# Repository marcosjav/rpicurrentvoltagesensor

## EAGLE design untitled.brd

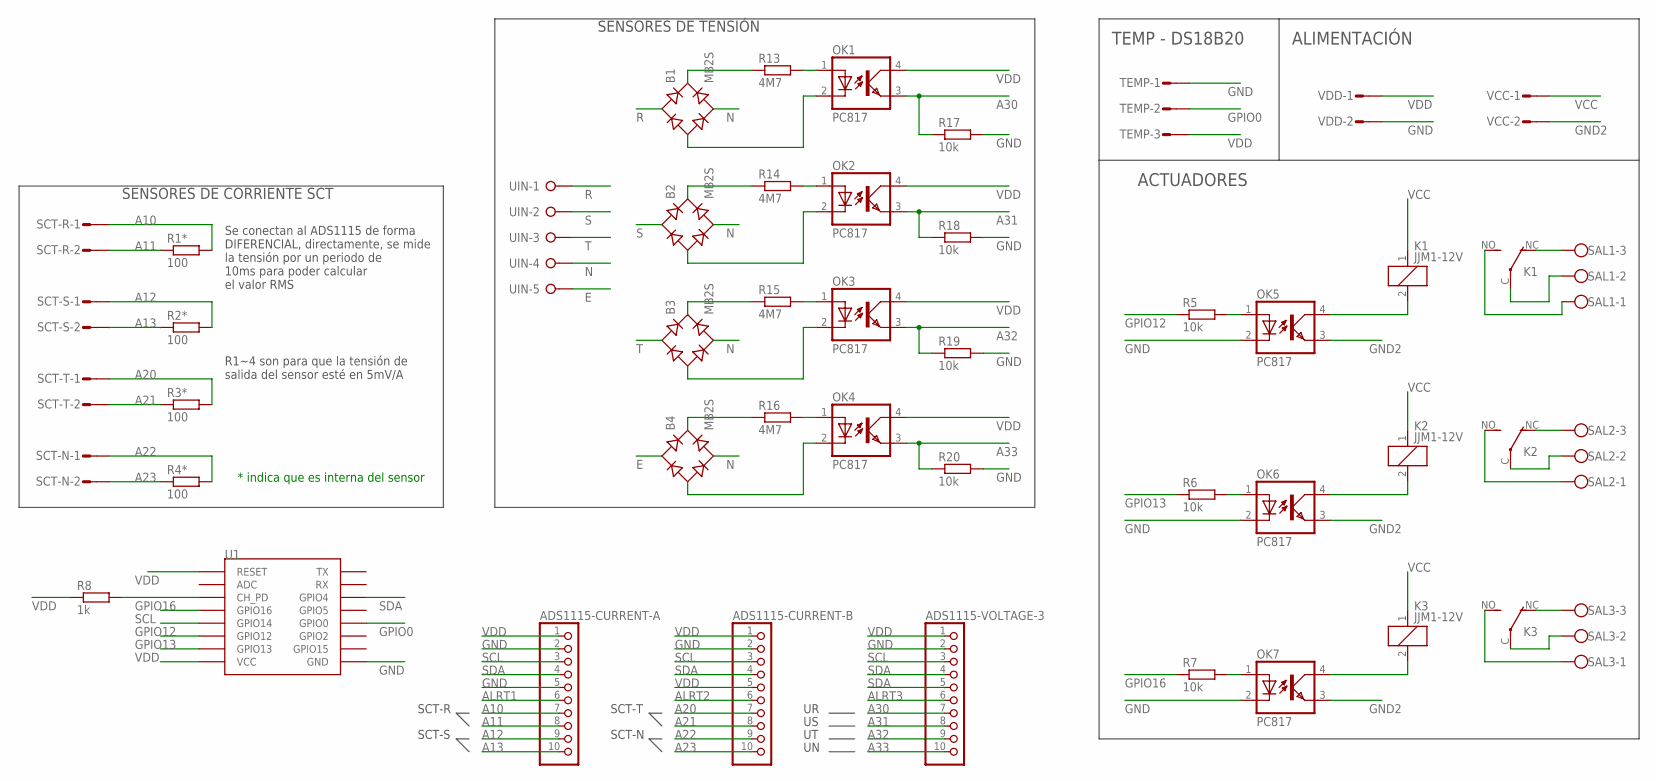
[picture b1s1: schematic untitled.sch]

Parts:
ADS1115-CURRENT-A, ADS1115-CURRENT-B, ADS1115-VOLTAGE-3: PINHD-1X10; 1X10
B1, B2, B3, B4: MB2S; SOIC-4
K1, K2, K3: JJM1-12V; JJM1C
OK1, OK2, OK3, OK4, OK5, OK6, OK7: PC817; DIL04
R1*, R2*, R3*, R4*: 100; M0805
R5, R6, R7, R17, R18, R19, R20: 10k; M0805
R8: 1k; M0805
R13, R14, R15, R16: 4M7; M0805
SAL1, SAL2, SAL3: W237-103
SCT-N: S02P
SCT-R: S02P
SCT-S: S02P
SCT-T: S02P
TEMP: S03P
U1: ESP12SMD; ESP12-SMD
UIN: W237-05P; W237-5P
VCC: S02P
VDD: S02P

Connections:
A10: ADS1115-CURRENT-A.7, R1*.2, SCT-R.1; also elsewhere on the board
A11: ADS1115-CURRENT-A.8, R1*.1, SCT-R.2; also elsewhere on the board
A12: ADS1115-CURRENT-A.9, R2*.2, SCT-S.1; also elsewhere on the board
A13: ADS1115-CURRENT-A.10, R2*.1, SCT-S.2; also elsewhere on the board
A20: ADS1115-CURRENT-B.7, R3*.2, SCT-T.1; also elsewhere on the board
A21: ADS1115-CURRENT-B.8, R3*.1, SCT-T.2; also elsewhere on the board
A22: ADS1115-CURRENT-B.9, R4*.2, SCT-N.1; also elsewhere on the board
A23: ADS1115-CURRENT-B.10, R4*.1, SCT-N.2; also elsewhere on the board
A30: ADS1115-VOLTAGE-3.7, OK1.3 (EMIT), R17.1
A31: ADS1115-VOLTAGE-3.8, OK2.3 (EMIT), R18.1
A32: ADS1115-VOLTAGE-3.9, OK3.3 (EMIT), R19.1
A33: ADS1115-VOLTAGE-3.10, OK4.3 (EMIT), R20.1
ALRT1: ADS1115-CURRENT-A.6
ALRT2: ADS1115-CURRENT-B.6
ALRT3: ADS1115-VOLTAGE-3.6
E: B4.~1 (AC1), UIN.5
GND: ADS1115-CURRENT-A.2, ADS1115-CURRENT-A.5, ADS1115-CURRENT-B.2, ADS1115-VOLTAGE-3.2, OK5.2 (C), OK6.2 (C), OK7.2 (C), R17.2, R18.2, R19.2, R20.2, TEMP.1, U1.GND, VDD.2
GND2: OK5.3 (EMIT), OK6.3 (EMIT), OK7.3 (EMIT), VCC.2
GPIO0: TEMP.2, U1.GPIO0
GPIO12: R5.1, U1.GPIO12
GPIO13: R6.1, U1.GPIO13
GPIO16: R7.1, U1.GPIO16
N: B1.~2 (AC2), B2.~2 (AC2), B3.~2 (AC2), B4.~2 (AC2), UIN.4
unnamed: K1.C, SAL1.2
unnamed: K1.NO (S), SAL1.1
unnamed: K1.NC (O), SAL1.3
unnamed: K1.2, OK5.4 (COL)
unnamed: K2.2, OK6.4 (COL)
unnamed: K3.2, OK7.4 (COL)
unnamed: OK5.1 (A), R5.2
unnamed: OK2.1 (A), R14.2
unnamed: OK1.1 (A), R13.2
unnamed: B2.+, R14.1
unnamed: B1.+, R13.1
unnamed: B1.-, OK1.2 (C)
unnamed: B2.-, OK2.2 (C)
unnamed: OK3.1 (A), R15.2
unnamed: B3.+, R15.1
unnamed: B3.-, OK3.2 (C)
unnamed: OK4.1 (A), R16.2
unnamed: B4.+, R16.1
unnamed: B4.-, OK4.2 (C)
unnamed: R8.2, U1.CH_PD
unnamed: K2.NC (O), SAL2.3
unnamed: K2.C, SAL2.2
unnamed: K2.NO (S), SAL2.1
unnamed: K3.C, SAL3.2
unnamed: K3.NC (O), SAL3.3
unnamed: K3.NO (S), SAL3.1
unnamed: OK6.1 (A), R6.2
unnamed: OK7.1 (A), R7.2
R: B1.~1 (AC1), UIN.1
S: B2.~1 (AC1), UIN.2
SCL: ADS1115-CURRENT-A.3, ADS1115-CURRENT-B.3, ADS1115-VOLTAGE-3.3, U1.GPIO14
SDA: ADS1115-CURRENT-A.4, ADS1115-CURRENT-B.4, ADS1115-VOLTAGE-3.4, ADS1115-VOLTAGE-3.5, U1.GPIO4
T: B3.~1 (AC1), UIN.3
VCC: K1.1, K2.1, K3.1, VCC.1
VDD: ADS1115-CURRENT-A.1, ADS1115-CURRENT-B.1, ADS1115-CURRENT-B.5, ADS1115-VOLTAGE-3.1, OK1.4 (COL), OK2.4 (COL), OK3.4 (COL), OK4.4 (COL), R8.1, TEMP.3, U1.RESET, U1.VCC, VDD.1

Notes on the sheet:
SCT-R
SCT-S
SCT-T
SCT-N
SENSORES DE CORRIENTE SCT
Se conectan al ADS1115 de forma DIFERENCIAL, directamente, se mide la tensión por un periodo de 10ms para poder calcular el valor RMS
R1~4 son para que la tensión de salida del sensor esté en 5mV/A
SENSORES DE TENSIÓN
ACTUADORES
TEMP - DS18B20
ALIMENTACIÓN
* indica que es interna del sensor

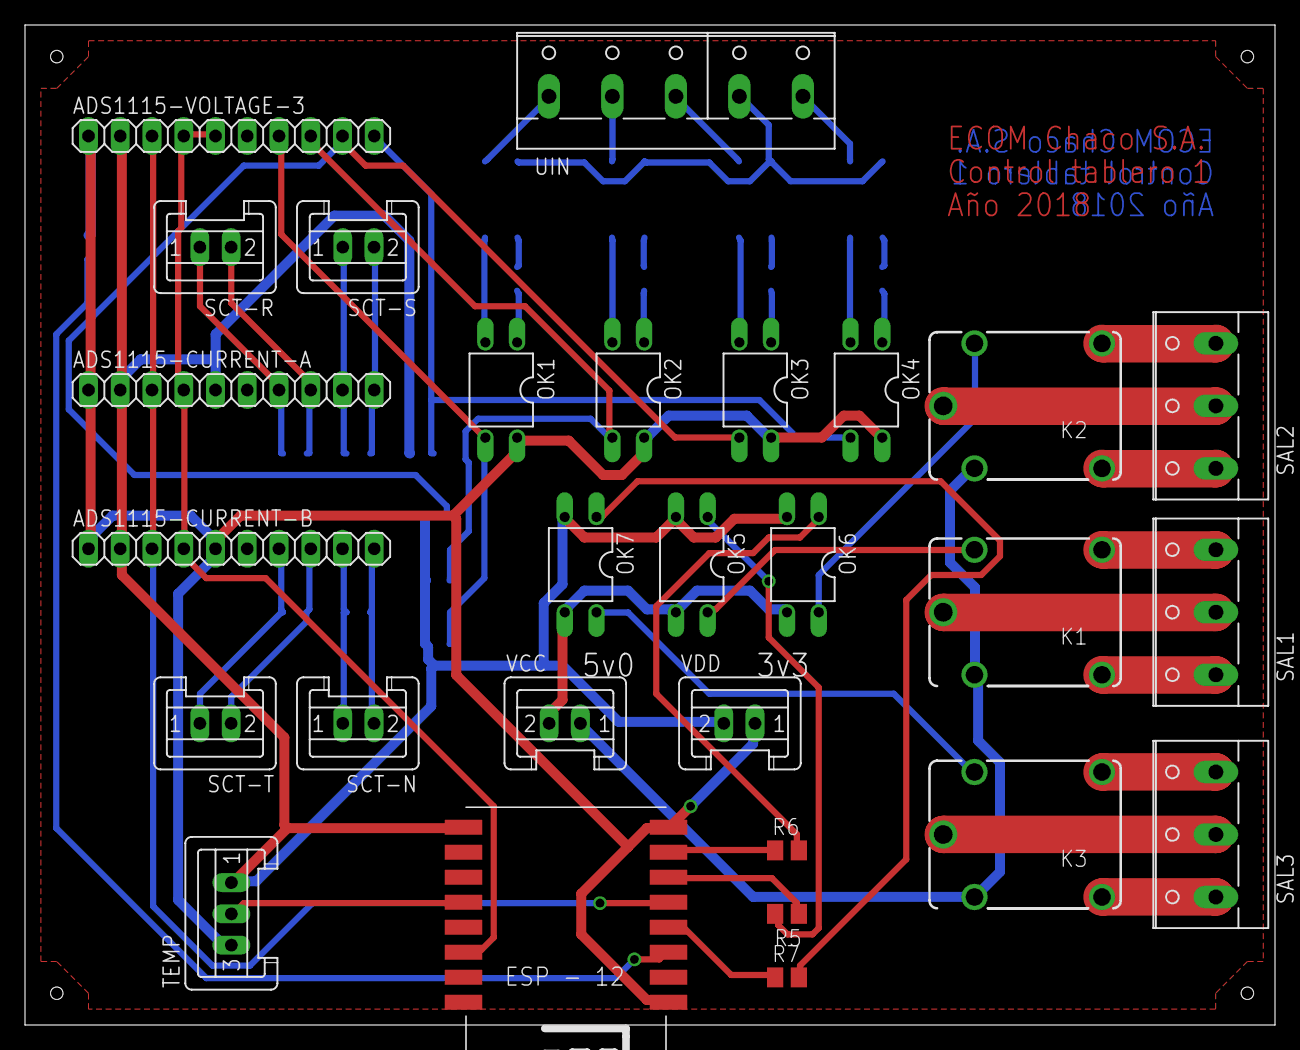
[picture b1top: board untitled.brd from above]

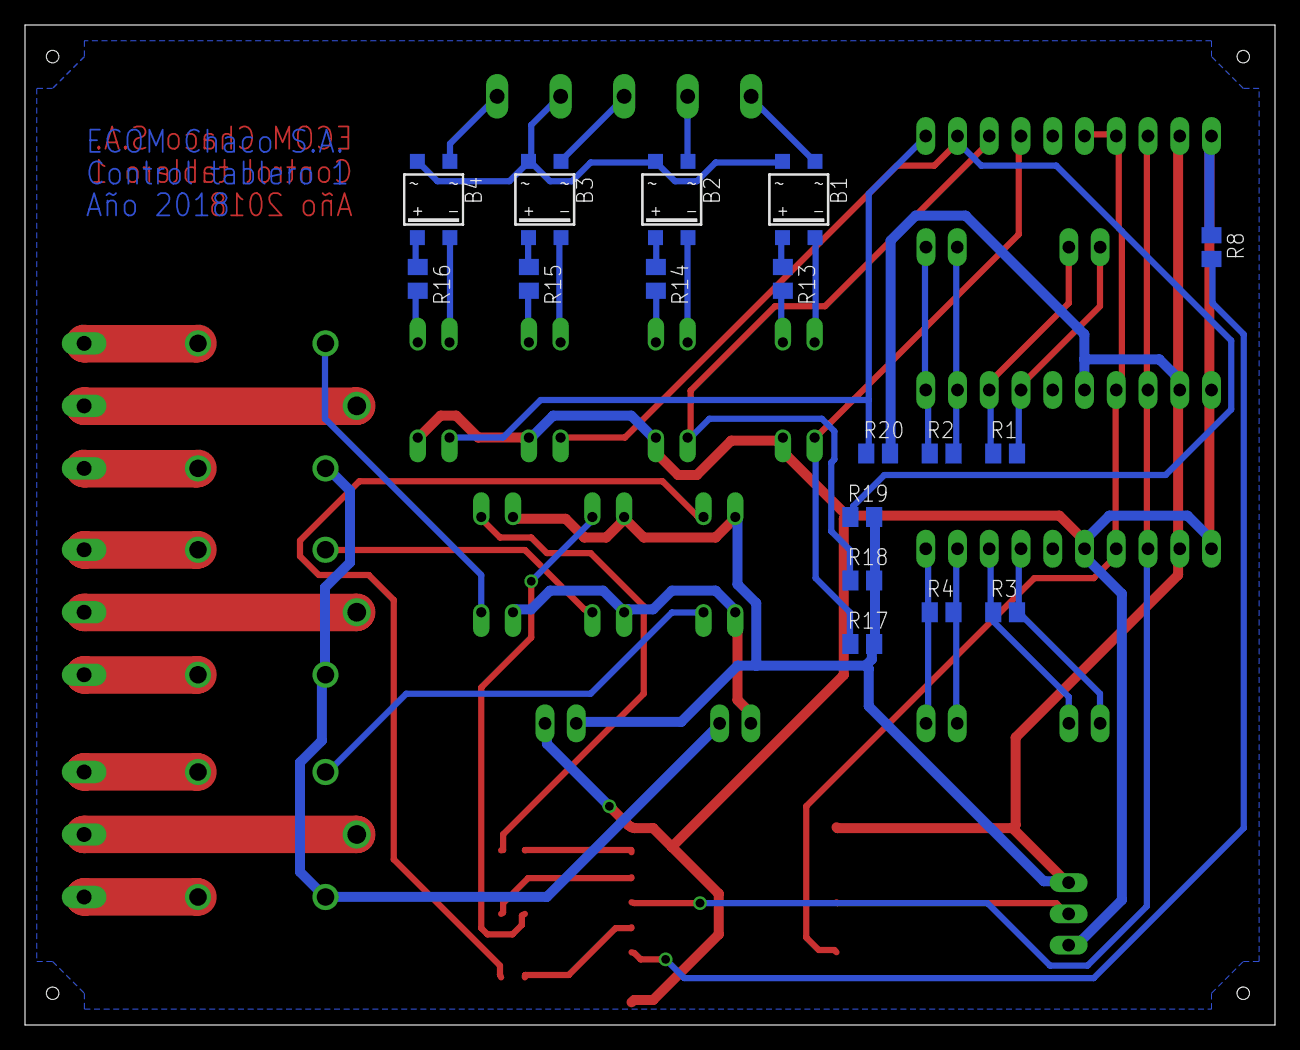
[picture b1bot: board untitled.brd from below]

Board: 2 copper layers, 100.0 x 80.0 mm, 45 parts (17 on the bottom side), 55 nets.

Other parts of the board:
R1, R2, R3, R4: 100; M0805

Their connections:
A10: R1.2; also elsewhere on the board
A11: R1.1; also elsewhere on the board
A12: R2.2; also elsewhere on the board
A13: R2.1; also elsewhere on the board
A20: R3.2; also elsewhere on the board
A21: R3.1; also elsewhere on the board
A22: R4.2; also elsewhere on the board
A23: R4.1; also elsewhere on the board

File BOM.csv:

Part;Value;Device;Package;Description
ADS1115-CURRENT-A;;PINHD-1X10;1X10;PIN HEADER
ADS1115-CURRENT-B;;PINHD-1X10;1X10;PIN HEADER
ADS1115-VOLTAGE-3;;PINHD-1X10;1X10;PIN HEADER
B1;MB2S;MB2S;SOIC-4;Bridge Rectifier
B2;MB2S;MB2S;SOIC-4;Bridge Rectifier
B3;MB2S;MB2S;SOIC-4;Bridge Rectifier
B4;MB2S;MB2S;SOIC-4;Bridge Rectifier
K1;JJM1-12V;JJM1-12V;JJM1C;HALF-SIZE AUTOMOTIVE RELAY NAiS
K2;JJM1-12V;JJM1-12V;JJM1C;HALF-SIZE AUTOMOTIVE RELAY NAiS
K3;JJM1-12V;JJM1-12V;JJM1C;HALF-SIZE AUTOMOTIVE RELAY NAiS
OK1;PC817;PC817;DIL04;SHARP OPTO COUPLER
OK2;PC817;PC817;DIL04;SHARP OPTO COUPLER
OK3;PC817;PC817;DIL04;SHARP OPTO COUPLER
OK4;PC817;PC817;DIL04;SHARP OPTO COUPLER
OK5;PC817;PC817;DIL04;SHARP OPTO COUPLER
OK6;PC817;PC817;DIL04;SHARP OPTO COUPLER
OK7;PC817;PC817;DIL04;SHARP OPTO COUPLER
R1*;100;R-EU_M0805;M0805;RESISTOR, European symbol
R2*;100;R-EU_M0805;M0805;RESISTOR, European symbol
R3*;100;R-EU_M0805;M0805;RESISTOR, European symbol
R4*;100;R-EU_M0805;M0805;RESISTOR, European symbol
R5;10k;R-EU_M0805;M0805;RESISTOR, European symbol
R6;10k;R-EU_M0805;M0805;RESISTOR, European symbol
R7;10k;R-EU_M0805;M0805;RESISTOR, European symbol
R8;1k;R-EU_M0805;M0805;RESISTOR, European symbol
R13;4M7;R-EU_M0805;M0805;RESISTOR, European symbol
R14;4M7;R-EU_M0805;M0805;RESISTOR, European symbol
R15;4M7;R-EU_M0805;M0805;RESISTOR, European symbol
R16;4M7;R-EU_M0805;M0805;RESISTOR, European symbol
R17;10k;R-EU_M0805;M0805;RESISTOR, European symbol
R18;10k;R-EU_M0805;M0805;RESISTOR, European symbol
R19;10k;R-EU_M0805;M0805;RESISTOR, European symbol
R20;10k;R-EU_M0805;M0805;RESISTOR, European symbol
SAL1;;W237-103;W237-103;WAGO SCREW CLAMP
SAL2;;W237-103;W237-103;WAGO SCREW CLAMP
SAL3;;W237-103;W237-103;WAGO SCREW CLAMP
SCT-N;;S02P;S02P;AMP MT CONNECTOR
SCT-R;;S02P;S02P;AMP MT CONNECTOR
SCT-S;;S02P;S02P;AMP MT CONNECTOR
SCT-T;;S02P;S02P;AMP MT CONNECTOR
TEMP;;S03P;S03P;AMP MT CONNECTOR
U1;;ESP12SMD;ESP12-SMD;ESP8266 Wifi module 12
UIN;;W237-05P;W237-5P;WAGO SREW CLAMP
VCC;;S02P;S02P;AMP MT CONNECTOR
VDD;;S02P;S02P;AMP MT CONNECTOR

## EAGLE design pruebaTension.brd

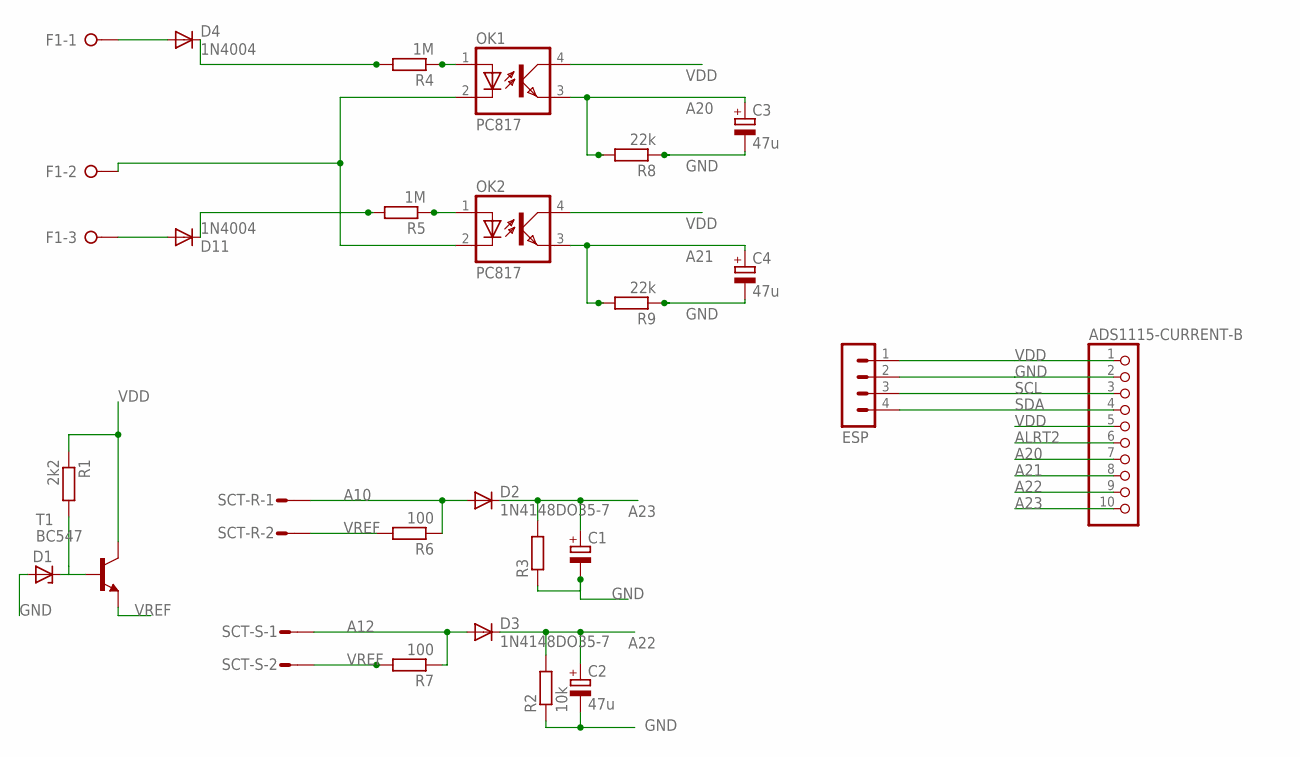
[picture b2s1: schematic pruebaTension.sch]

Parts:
ADS1115-CURRENT-B: PINHD-1X10; 1X10
C1: CPOL-EUE2.5-7; E2,5-7
C2, C3, C4: 47u; E2,5-7
D1: ZENER-DIODEZD-2.5; ZDIO-2.5
D2, D3: 1N4148DO35-7; DO35-7
D4, D11: 1N4004; DO41-10
ESP: MA04-1
F1: W237-3E
OK1, OK2: PC817; DIL04
R1: 2k2; 0204V
R2: 10k; 0204V
R3: R-EU_0204/2V; 0204V
R4, R5: 1M; 0204V
R6, R7: 100; 0204V
R8, R9: 22k; 0204V
SCT-R: S02P
SCT-S: S02P
T1: BC547; TO92

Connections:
A10: D2.A, R6.1, SCT-R.1
A12: D3.A, R7.1, SCT-S.1
A20: ADS1115-CURRENT-B.7, C3.+, OK1.3 (EMIT), R8.2
A21: ADS1115-CURRENT-B.8, C4.+, OK2.3 (EMIT), R9.2
A22: ADS1115-CURRENT-B.9, C2.+, D3.C, R2.2
A23: ADS1115-CURRENT-B.10, C1.+, D2.C, R3.2
ALRT2: ADS1115-CURRENT-B.6
GND: ADS1115-CURRENT-B.2, C1.-, C2.-, C3.-, C4.-, D1.A, ESP.2, R2.1, R3.1, R8.1, R9.1
unnamed: D11.A, F1.3
unnamed: D1.C, R1.2, T1.2 (B)
unnamed: F1.2, OK1.2 (C), OK2.2 (C)
unnamed: D4.A, F1.1
unnamed: OK2.1 (A), R5.1
unnamed: OK1.1 (A), R4.1
unnamed: D11.C, R5.2
unnamed: D4.C, R4.2
SCL: ADS1115-CURRENT-B.3, ESP.3
SDA: ADS1115-CURRENT-B.4, ESP.4
VDD: ADS1115-CURRENT-B.1, ADS1115-CURRENT-B.5, ESP.1, OK1.4 (COL), OK2.4 (COL), R1.1, T1.3 (C)
VREF: R6.2, R7.2, SCT-R.2, SCT-S.2, T1.1 (E)

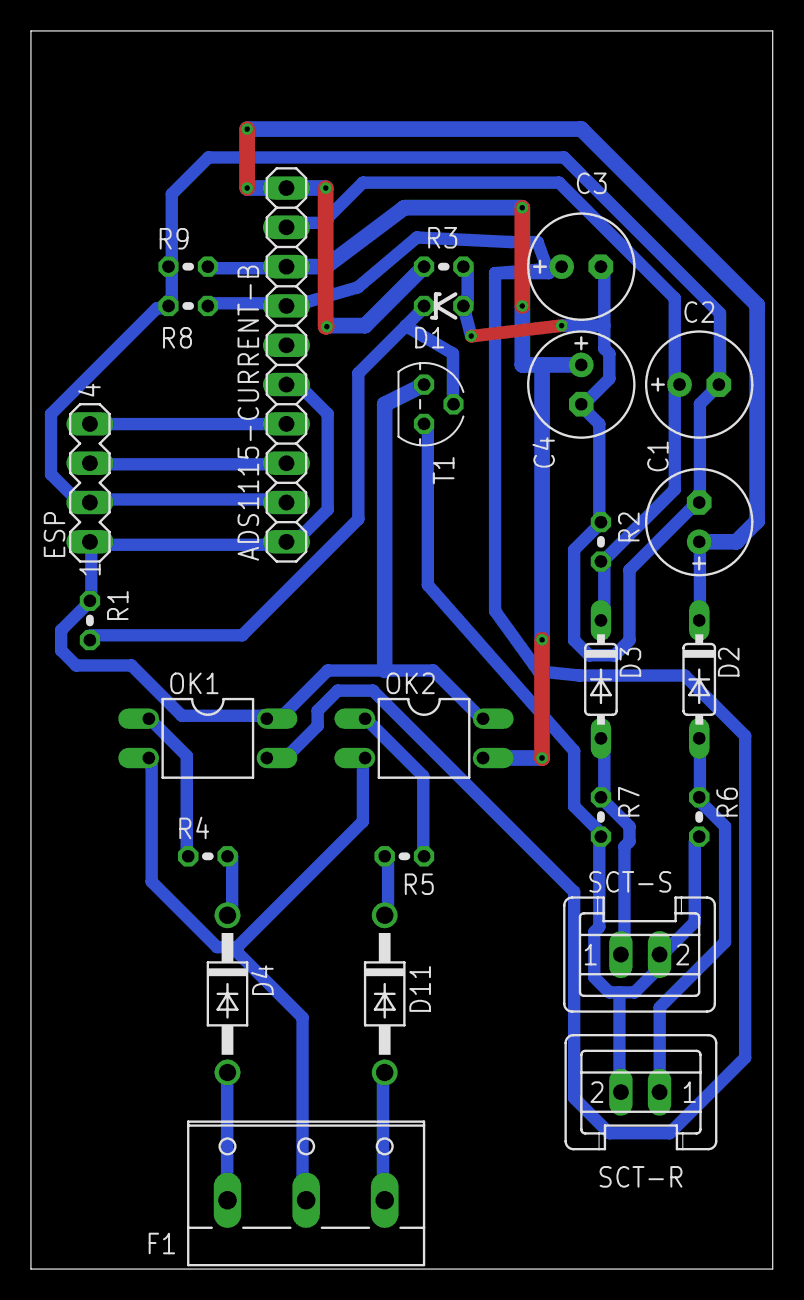
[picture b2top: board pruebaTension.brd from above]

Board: 2 copper layers, 47.9 x 80.0 mm, 26 parts (0 on the bottom side), 19 nets.

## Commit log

2019-03-15 Sensor de tensión y corriente para rpi
